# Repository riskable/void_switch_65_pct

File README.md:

# Void Switch Reference PCB Implementation

A reference implementation of an analog hall effect keyboard (65%) that uses 3D printed Void Switches and a Black Pill (STM32F4x1CEU6) microcontroller board.

__WARNING:__ I haven't had a chance to order and test this yet!  Use at your own risk!  YOU HAVE BEEN WARNED!

Inside this repository is a Kicad 6 project that has everything you need to get started making an analog keyboard PCB that uses 3D printed [Void Switches](https://github.com/riskable/void_switch).  It was made as part of a tutorial that is currently being worked on.  In the mean time--if you know what you're doing--feel to use it as a reference for creating your own analog keyboard PCBs.

# Included footprints and symbols

The [void_switch_kicad](https://github.com/riskable/void_switch_kicad) repository was added as a `git submodule` so don't forget to run `git submodule foreach git pull` from time to time in order to make sure it stays up-to-date.

There's also:

 * `kicad_misc_parts` which for now just includes a single footprint for a vertical QWIIC/4-pin JST connector that happens to be easy to obtain right now (damn you, parts shortage!).
 * `kicad_blackpill` which contains a simple symbol and footprint for the WeAct Studio Black Pill board.  If you're wondering about the staggered pins it's just a neat way to make hand-soldering a bit easier (it holds the headers in place while you solder; so they won't shift around/lean/fall out).

# Tutorial and OpenSCAD case/plate files are coming soon!

Remember folks: This is my hobby, not my full time job =)

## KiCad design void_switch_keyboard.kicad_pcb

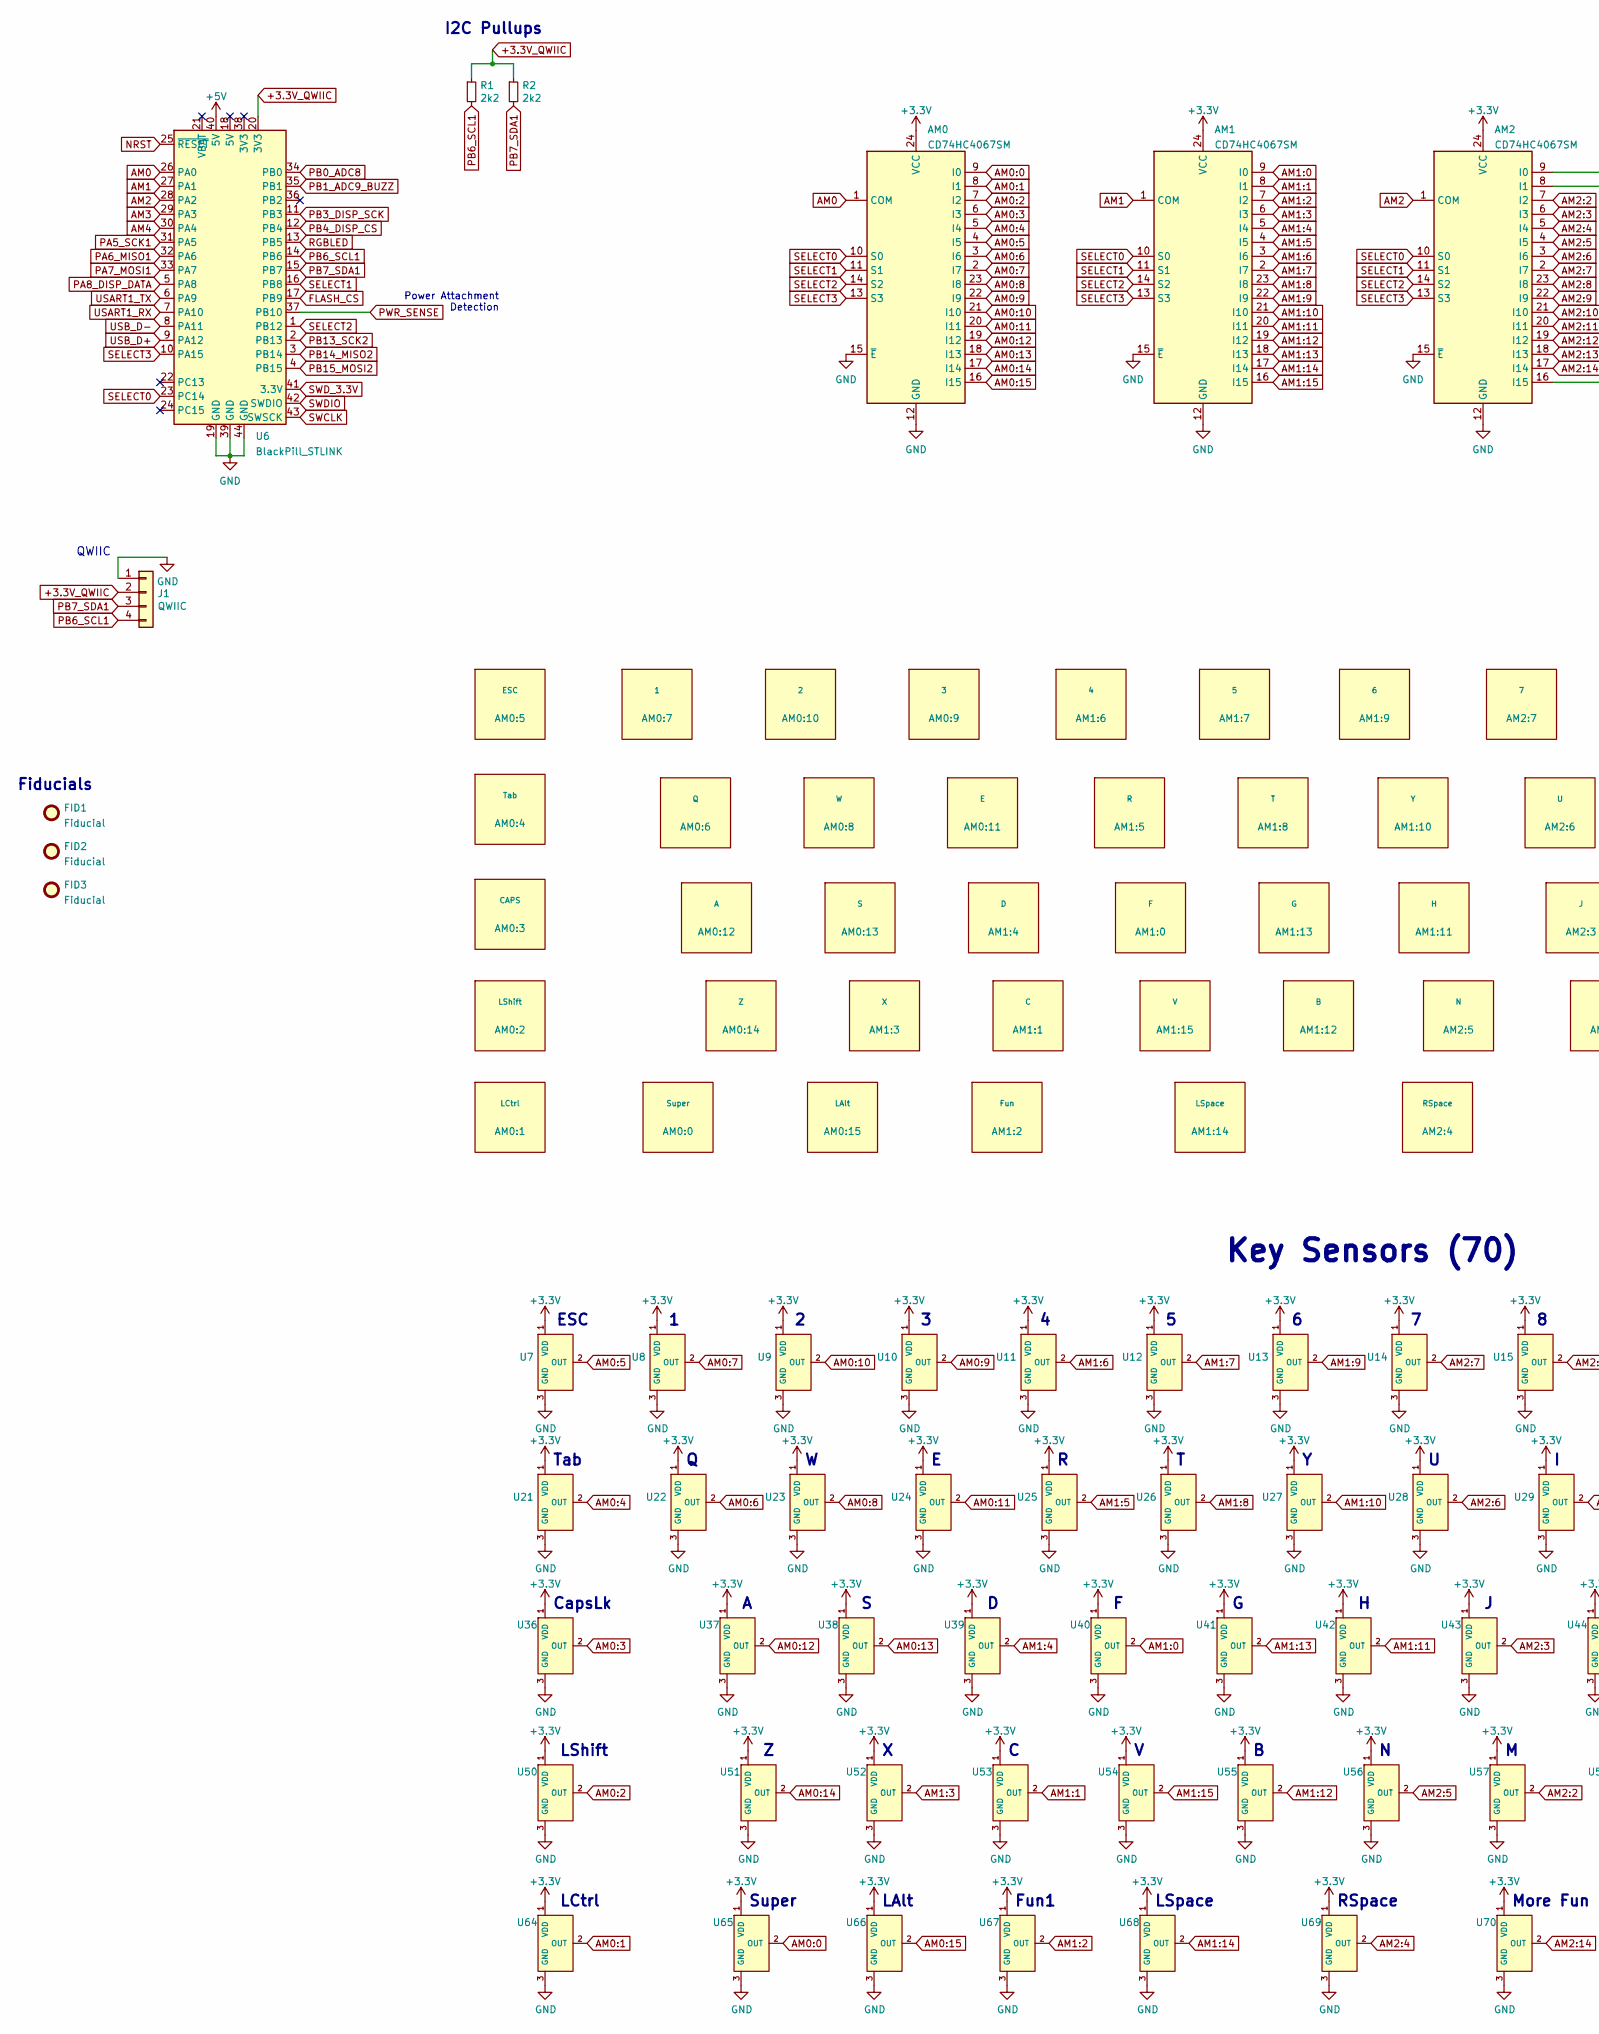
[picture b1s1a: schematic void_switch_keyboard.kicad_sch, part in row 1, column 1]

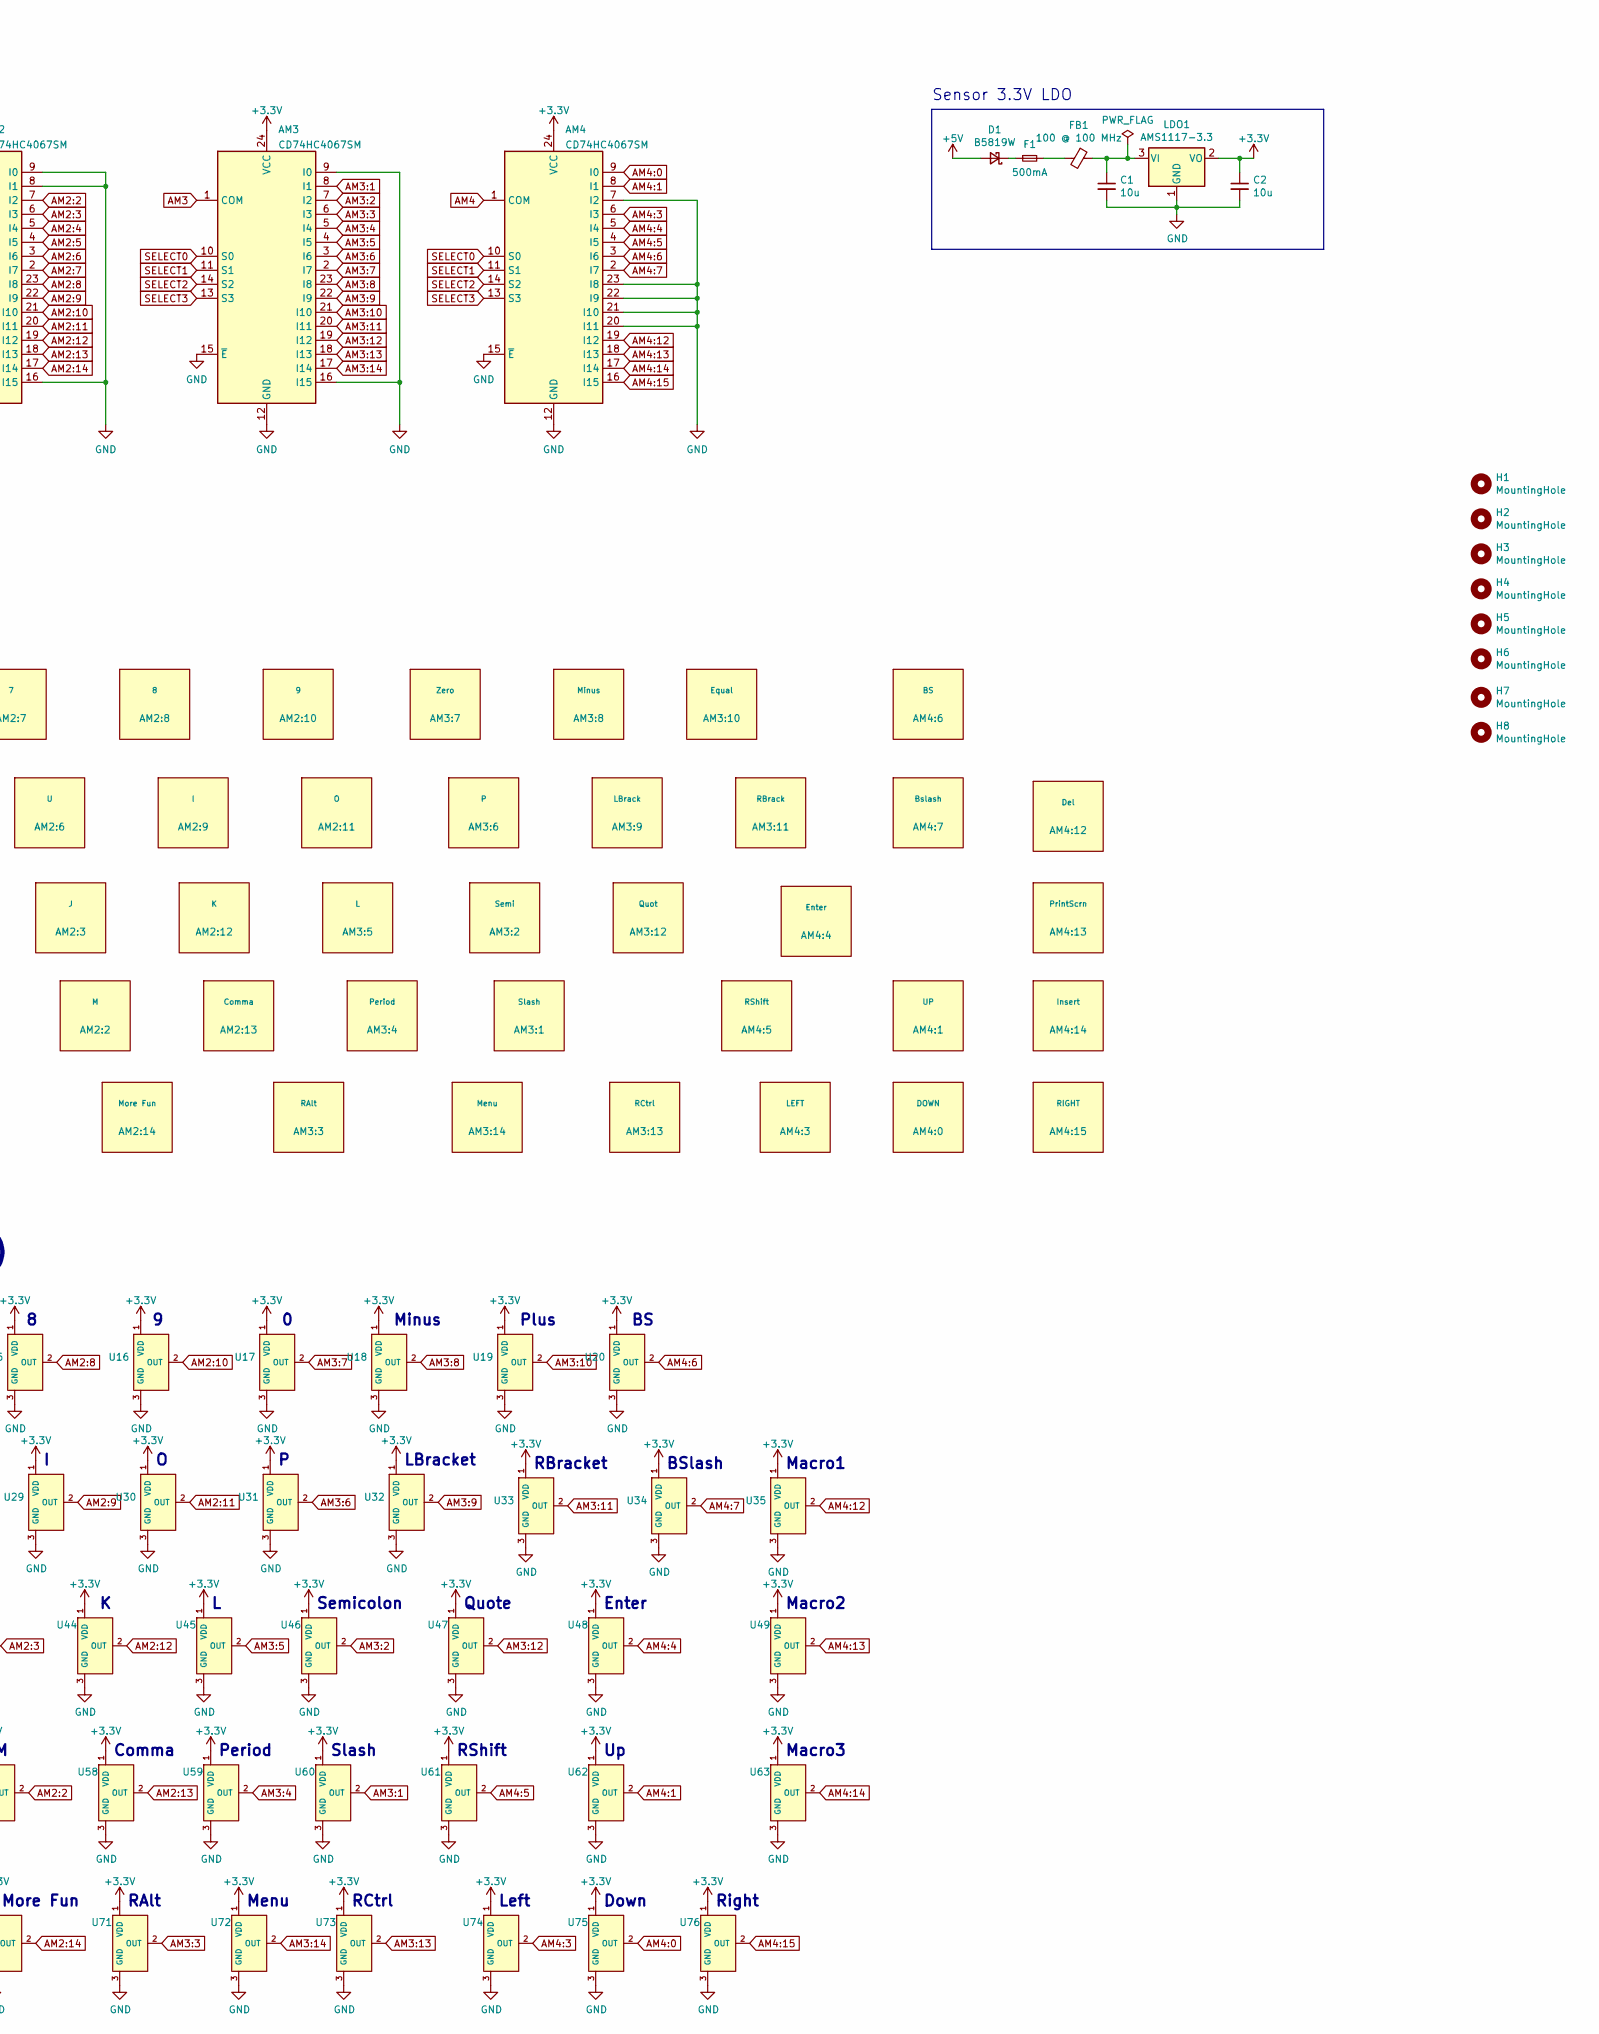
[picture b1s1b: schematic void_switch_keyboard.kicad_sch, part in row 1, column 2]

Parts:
AM0, AM1, AM2, AM3, AM4: CD74HC4067SM; SSOP-24_5.3x8.2mm_P0.65mm
AM0:0: Super; VoidSwitch_1.25u_SMD
AM0:1: LCtrl; VoidSwitch_1.25u_SMD
AM0:2: LShift; VoidSwitch_1u_SMD
AM0:3: CAPS; VoidSwitch_1u_SMD
AM0:4: Tab; VoidSwitch_1u_SMD
AM0:5: ESC; VoidSwitch_1u_SMD
AM0:6: Q; VoidSwitch_1u_SMD
AM0:7: 1; VoidSwitch_1u_SMD
AM0:8: W; VoidSwitch_1u_SMD
AM0:9: 3; VoidSwitch_1u_SMD
AM0:10: 2; VoidSwitch_1u_SMD
AM0:11: E; VoidSwitch_1u_SMD
AM0:12: A; VoidSwitch_1u_SMD
AM0:13: S; VoidSwitch_1u_SMD
AM0:14: Z; VoidSwitch_1u_SMD
AM0:15: LAlt; VoidSwitch_1.25u_SMD
AM1:0: F; VoidSwitch_1u_SMD
AM1:1: C; VoidSwitch_1u_SMD
AM1:2: Fun; VoidSwitch_1.25u_SMD
AM1:3: X; VoidSwitch_1u_SMD
AM1:4: D; VoidSwitch_1u_SMD
AM1:5: R; VoidSwitch_1u_SMD
AM1:6: 4; VoidSwitch_1u_SMD
AM1:7: 5; VoidSwitch_1u_SMD
AM1:8: T; VoidSwitch_1u_SMD
AM1:9: 6; VoidSwitch_1u_SMD
AM1:10: Y; VoidSwitch_1u_SMD
AM1:11: H; VoidSwitch_1u_SMD
AM1:12: B; VoidSwitch_1u_SMD
AM1:13: G; VoidSwitch_1u_SMD
AM1:14: LSpace; VoidSwitch_1u_SMD
AM1:15: V; VoidSwitch_1u_SMD
AM2:2: M; VoidSwitch_1u_SMD
AM2:3: J; VoidSwitch_1u_SMD
AM2:4: RSpace; VoidSwitch_1u_SMD
AM2:5: N; VoidSwitch_1u_SMD
AM2:6: U; VoidSwitch_1u_SMD
AM2:7: 7; VoidSwitch_1u_SMD
AM2:8: 8; VoidSwitch_1u_SMD
AM2:9: I; VoidSwitch_1u_SMD
AM2:10: 9; VoidSwitch_1u_SMD
AM2:11: O; VoidSwitch_1u_SMD
AM2:12: K; VoidSwitch_1u_SMD
AM2:13: Comma; VoidSwitch_1u_SMD
AM2:14: More Fun; VoidSwitch_1.25u_SMD
AM3:1: Slash; VoidSwitch_1u_SMD
AM3:2: Semi; VoidSwitch_1u_SMD
AM3:3: RAlt; VoidSwitch_1.25u_SMD
AM3:4: Period; VoidSwitch_1u_SMD
AM3:5: L; VoidSwitch_1u_SMD
AM3:6: P; VoidSwitch_1u_SMD
AM3:7: Zero; VoidSwitch_1u_SMD
AM3:8: Minus; VoidSwitch_1u_SMD
AM3:9: LBrack; VoidSwitch_1u_SMD
AM3:10: Equal; VoidSwitch_1u_SMD
AM3:11: RBrack; VoidSwitch_1u_SMD
AM3:12: Quot; VoidSwitch_1u_SMD
AM3:13: RCtrl; VoidSwitch_1u_SMD
AM3:14: Menu; VoidSwitch_1u_SMD
AM4:0: DOWN; VoidSwitch_1u_SMD
AM4:1: UP; VoidSwitch_1u_SMD
AM4:3: LEFT; VoidSwitch_1u_SMD
AM4:4: Enter; VoidSwitch_1u_SMD
AM4:5: RShift; VoidSwitch_1u_SMD
AM4:6: BS; VoidSwitch_1u_SMD
AM4:7: Bslash; VoidSwitch_1u_SMD
AM4:12: Del; VoidSwitch_1u_SMD
AM4:13: PrintScrn; VoidSwitch_1u_SMD
AM4:14: Insert; VoidSwitch_1u_SMD
AM4:15: RIGHT; VoidSwitch_1u_SMD
C1, C2: 10u; C_0402_1005Metric; MPN CL05A106MQ5NUNC; LCSC Part C15525
D1: B5819W; D_SOD-123; MPN B5819W; LCSC Part C8598
F1: 500mA; Fuse_0603_1608Metric; LCSC Part C261937
FB1: 100 @ 100 MHz; L_0805_2012Metric; MPN GZ2012D101TF; LCSC Part C1015
FID1, FID2, FID3: Fiducial; Fiducial_1mm_Mask2mm
H1, H2, H3, H4, H5, H6, H7, H8: MountingHole; MountingHole_3.2mm_M3_Pad
J1: QWIIC; JST_SH_BM04B-SRSS-TB_1x04-1MP_P1.00mm_Vertical; LCSC Part C160404
LDO1: AMS1117-3.3; SOT-223-3_TabPin2; MPN AMS1117-3.3; LCSC Part C6186
R1, R2: 2k2; R_0402_1005Metric; MPN 0402WGF2201TCE; LCSC Part C25879
U6: BlackPill_STLINK
U7, U8, U9, U10, U11, U12, U13, U14, U15, U16, U17, U18, U19, U20, U21, U22, U23, U24, U25, U26, U27, U28, U29, U30, U31, U32, U33, U34, U35, U36, U37, U38, U39, U40, U41, U42, U43, U44, U45, U46, U47, U48, U49, U50, U51, U52, U53, U54, U55, U56, U57, U58, U59, U60, U61, U62, U63, U64, U65, U66, U67, U68, U69, U70, U71, U72, U73, U74, U75, U76: GH39FKSW; SOT-23; MPN GH39FKSW; LCSC Part C266230

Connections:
+3.3V_QWIIC: J1.2, R1.1, R2.1, U6.20 (3V3)
+3V3: AM0.24 (VCC), AM1.24 (VCC), AM2.24 (VCC), AM3.24 (VCC), AM4.24 (VCC), C2.1, LDO1.2 (VO), U7.1 (VDD), U8.1 (VDD), U9.1 (VDD), U10.1 (VDD), U11.1 (VDD), U12.1 (VDD), U13.1 (VDD), U14.1 (VDD), U15.1 (VDD), U16.1 (VDD), U17.1 (VDD), U18.1 (VDD), U19.1 (VDD), U20.1 (VDD), U21.1 (VDD), U22.1 (VDD), U23.1 (VDD), U24.1 (VDD), U25.1 (VDD), U26.1 (VDD), U27.1 (VDD), U28.1 (VDD), U29.1 (VDD), U30.1 (VDD), U31.1 (VDD), U32.1 (VDD), U33.1 (VDD), U34.1 (VDD), U35.1 (VDD), U36.1 (VDD), U37.1 (VDD), U38.1 (VDD), U39.1 (VDD), U40.1 (VDD), U41.1 (VDD), U42.1 (VDD), U43.1 (VDD), U44.1 (VDD), U45.1 (VDD), U46.1 (VDD), U47.1 (VDD), U48.1 (VDD), U49.1 (VDD), U50.1 (VDD), U51.1 (VDD), U52.1 (VDD), U53.1 (VDD), U54.1 (VDD), U55.1 (VDD), U56.1 (VDD), U57.1 (VDD), U58.1 (VDD), U59.1 (VDD), U60.1 (VDD), U61.1 (VDD), U62.1 (VDD), U63.1 (VDD), U64.1 (VDD), U65.1 (VDD), U66.1 (VDD), U67.1 (VDD), U68.1 (VDD), U69.1 (VDD), U70.1 (VDD), U71.1 (VDD), U72.1 (VDD), U73.1 (VDD), U74.1 (VDD), U75.1 (VDD), U76.1 (VDD)
+5V: D1.2 (A), U6.40 (5V)
AM0: AM0.1 (COM), U6.26 (PA0)
AM0:0: AM0.9 (I0), U65.2 (OUT)
AM0:1: AM0.8 (I1), U64.2 (OUT)
AM0:2: AM0.7 (I2), U50.2 (OUT)
AM0:3: AM0.6 (I3), U36.2 (OUT)
AM0:4: AM0.5 (I4), U21.2 (OUT)
AM0:5: AM0.4 (I5), U7.2 (OUT)
AM0:6: AM0.3 (I6), U22.2 (OUT)
AM0:7: AM0.2 (I7), U8.2 (OUT)
AM0:8: AM0.23 (I8), U23.2 (OUT)
AM0:9: AM0.22 (I9), U10.2 (OUT)
AM0:10: AM0.21 (I10), U9.2 (OUT)
AM0:11: AM0.20 (I11), U24.2 (OUT)
AM0:12: AM0.19 (I12), U37.2 (OUT)
AM0:13: AM0.18 (I13), U38.2 (OUT)
AM0:14: AM0.17 (I14), U51.2 (OUT)
AM0:15: AM0.16 (I15), U66.2 (OUT)
AM1: AM1.1 (COM), U6.27 (PA1)
AM1:0: AM1.9 (I0), U40.2 (OUT)
AM1:1: AM1.8 (I1), U53.2 (OUT)
AM1:2: AM1.7 (I2), U67.2 (OUT)
AM1:3: AM1.6 (I3), U52.2 (OUT)
AM1:4: AM1.5 (I4), U39.2 (OUT)
AM1:5: AM1.4 (I5), U25.2 (OUT)
AM1:6: AM1.3 (I6), U11.2 (OUT)
AM1:7: AM1.2 (I7), U12.2 (OUT)
AM1:8: AM1.23 (I8), U26.2 (OUT)
AM1:9: AM1.22 (I9), U13.2 (OUT)
AM1:10: AM1.21 (I10), U27.2 (OUT)
AM1:11: AM1.20 (I11), U42.2 (OUT)
AM1:12: AM1.19 (I12), U55.2 (OUT)
AM1:13: AM1.18 (I13), U41.2 (OUT)
AM1:14: AM1.17 (I14), U68.2 (OUT)
AM1:15: AM1.16 (I15), U54.2 (OUT)
AM2: AM2.1 (COM), U6.28 (PA2)
AM2:2: AM2.7 (I2), U57.2 (OUT)
AM2:3: AM2.6 (I3), U43.2 (OUT)
AM2:4: AM2.5 (I4), U69.2 (OUT)
AM2:5: AM2.4 (I5), U56.2 (OUT)
AM2:6: AM2.3 (I6), U28.2 (OUT)
AM2:7: AM2.2 (I7), U14.2 (OUT)
AM2:8: AM2.23 (I8), U15.2 (OUT)
AM2:9: AM2.22 (I9), U29.2 (OUT)
AM2:10: AM2.21 (I10), U16.2 (OUT)
AM2:11: AM2.20 (I11), U30.2 (OUT)
AM2:12: AM2.19 (I12), U44.2 (OUT)
AM2:13: AM2.18 (I13), U58.2 (OUT)
AM2:14: AM2.17 (I14), U70.2 (OUT)
AM3: AM3.1 (COM), U6.29 (PA3)
AM3:1: AM3.8 (I1), U60.2 (OUT)
AM3:2: AM3.7 (I2), U46.2 (OUT)
AM3:3: AM3.6 (I3), U71.2 (OUT)
AM3:4: AM3.5 (I4), U59.2 (OUT)
AM3:5: AM3.4 (I5), U45.2 (OUT)
AM3:6: AM3.3 (I6), U31.2 (OUT)
AM3:7: AM3.2 (I7), U17.2 (OUT)
AM3:8: AM3.23 (I8), U18.2 (OUT)
AM3:9: AM3.22 (I9), U32.2 (OUT)
AM3:10: AM3.21 (I10), U19.2 (OUT)
AM3:11: AM3.20 (I11), U33.2 (OUT)
AM3:12: AM3.19 (I12), U47.2 (OUT)
AM3:13: AM3.18 (I13), U73.2 (OUT)
AM3:14: AM3.17 (I14), U72.2 (OUT)
AM4: AM4.1 (COM), U6.30 (PA4)
AM4:0: AM4.9 (I0), U75.2 (OUT)
AM4:1: AM4.8 (I1), U62.2 (OUT)
AM4:3: AM4.6 (I3), U74.2 (OUT)
AM4:4: AM4.5 (I4), U48.2 (OUT)
AM4:5: AM4.4 (I5), U61.2 (OUT)
AM4:6: AM4.3 (I6), U20.2 (OUT)
AM4:7: AM4.2 (I7), U34.2 (OUT)
AM4:12: AM4.19 (I12), U35.2 (OUT)
AM4:13: AM4.18 (I13), U49.2 (OUT)
AM4:14: AM4.17 (I14), U63.2 (OUT)
AM4:15: AM4.16 (I15), U76.2 (OUT)
FLASH_CS: U6.17 (PB9)
GND: AM0.12 (GND), AM0.15 (~E), AM1.12 (GND), AM1.15 (~E), AM2.8 (I1), AM2.9 (I0), AM2.12 (GND), AM2.15 (~E), AM2.16 (I15), AM3.9 (I0), AM3.12 (GND), AM3.15 (~E), AM3.16 (I15), AM4.7 (I2), AM4.12 (GND), AM4.15 (~E), AM4.20 (I11), AM4.21 (I10), AM4.22 (I9), AM4.23 (I8), C1.2, C2.2, J1.1, LDO1.1 (GND), U6.19 (GND), U6.39 (GND), U6.44 (GND), U7.3 (GND), U8.3 (GND), U9.3 (GND), U10.3 (GND), U11.3 (GND), U12.3 (GND), U13.3 (GND), U14.3 (GND), U15.3 (GND), U16.3 (GND), U17.3 (GND), U18.3 (GND), U19.3 (GND), U20.3 (GND), U21.3 (GND), U22.3 (GND), U23.3 (GND), U24.3 (GND), U25.3 (GND), U26.3 (GND), U27.3 (GND), U28.3 (GND), U29.3 (GND), U30.3 (GND), U31.3 (GND), U32.3 (GND), U33.3 (GND), U34.3 (GND), U35.3 (GND), U36.3 (GND), U37.3 (GND), U38.3 (GND), U39.3 (GND), U40.3 (GND), U41.3 (GND), U42.3 (GND), U43.3 (GND), U44.3 (GND), U45.3 (GND), U46.3 (GND), U47.3 (GND), U48.3 (GND), U49.3 (GND), U50.3 (GND), U51.3 (GND), U52.3 (GND), U53.3 (GND), U54.3 (GND), U55.3 (GND), U56.3 (GND), U57.3 (GND), U58.3 (GND), U59.3 (GND), U60.3 (GND), U61.3 (GND), U62.3 (GND), U63.3 (GND), U64.3 (GND), U65.3 (GND), U66.3 (GND), U67.3 (GND), U68.3 (GND), U69.3 (GND), U70.3 (GND), U71.3 (GND), U72.3 (GND), U73.3 (GND), U74.3 (GND), U75.3 (GND), U76.3 (GND)
NRST: U6.25 (~RESET)
unnamed: C1.1, FB1.1, LDO1.3 (VI)
unnamed: D1.1 (K), F1.1
unnamed: F1.2, FB1.2
PA5_SCK1: U6.31 (PA5)
PA6_MISO1: U6.32 (PA6)
PA7_MOSI1: U6.33 (PA7)
PA8_DISP_DATA: U6.5 (PA8)
PB0_ADC8: U6.34 (PB0)
PB1_ADC9_BUZZ: U6.35 (PB1)
PB3_DISP_SCK: U6.11 (PB3)
PB4_DISP_CS: U6.12 (PB4)
PB6_SCL1: J1.4, R1.2, U6.14 (PB6)
PB7_SDA1: J1.3, R2.2, U6.15 (PB7)
PB13_SCK2: U6.2 (PB13)
PB14_MISO2: U6.3 (PB14)
PB15_MOSI2: U6.4 (PB15)
PWR_SENSE: U6.37 (PB10)
RGBLED: U6.13 (PB5)
SELECT0: AM0.10 (S0), AM1.10 (S0), AM2.10 (S0), AM3.10 (S0), AM4.10 (S0), U6.23 (PC14)
SELECT1: AM0.11 (S1), AM1.11 (S1), AM2.11 (S1), AM3.11 (S1), AM4.11 (S1), U6.16 (PB8)
SELECT2: AM0.14 (S2), AM1.14 (S2), AM2.14 (S2), AM3.14 (S2), AM4.14 (S2), U6.1 (PB12)
SELECT3: AM0.13 (S3), AM1.13 (S3), AM2.13 (S3), AM3.13 (S3), AM4.13 (S3), U6.10 (PA15)
SWCLK: U6.43 (SWSCK)
SWDIO: U6.42 (SWDIO)
SWD_3.3V: U6.41 (3.3V)
USART1_RX: U6.7 (PA10)
USART1_TX: U6.6 (PA9)
USB_D+: U6.9 (PA12)
USB_D-: U6.8 (PA11)

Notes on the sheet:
LAlt
Plus
RShift
LShift
RAlt
RSpace
RCtrl
CapsLk
More Fun
Tab
Down
Macro2
Semicolon
Comma
Enter
Super
RBracket
Right
BSlash
LCtrl
Power Attachment Detection
QWIIC
Fiducials
Minus
LSpace
Left
Slash
Key Sensors (70)
Fun1
Macro1
Macro3
Quote
Period
Menu
I2C Pullups
LBracket
Sensor 3.3V LDO
ESC

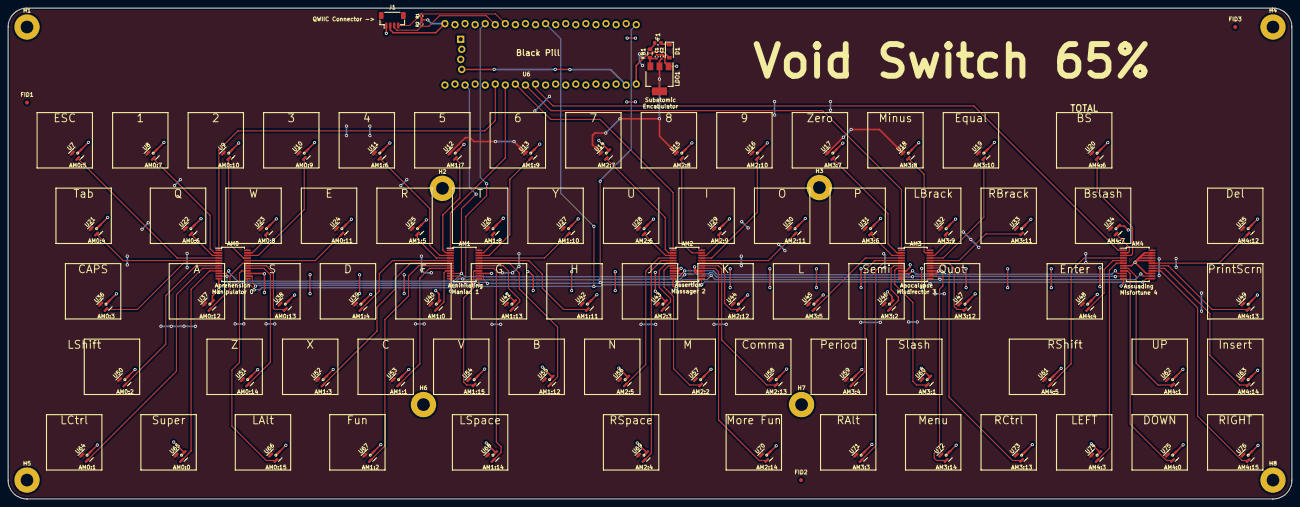
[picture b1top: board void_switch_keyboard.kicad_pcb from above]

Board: 2 copper layers, 323.9 x 123.8 mm, 167 parts (1 on the bottom side), 88 nets.

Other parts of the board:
QR*****: https://github.com/riskable/void_switch; VoidSwitch_Repo_QR_0.5mm

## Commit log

2022-01-17 Initial commit.
2022-01-17 Added warning to the README about how I haven't had a chance to order/test this board yet.
2022-01-20 Updated silkscreen and fixed the analog multiplexer references so they're AM0-AM4 instead of U1-U5.
2022-01-20 Fixed a few minor issues with the silkscreen and added the void_switch repo QR code to the back.
2022-01-24 Fixed the 1.25U keys having 1U footprints.
2022-01-24 Fixed AM0:0 and AM0:1 being left floating. They're now connected to ground as they should be (because they're unused).
2022-02-06 Fixed a MUX pins that was left floating and added a bit of 3.3V and GND stitching to shorten the power/ground path here and there.
